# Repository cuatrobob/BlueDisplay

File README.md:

# BlueDisplay
Simple execution for controlling an LED display with Android devices via Bluetooth LE.

The system is controlled by Arduino Uno, the communication is handled by HM-11 Bluetooth 4.0 module, and the display module is DFRobot LCD4884. Since LCD4884 takes up D2 through D7 it will not conflict with the Bluetooth module. In order to monitor serial I/O at the same time, SoftwareSerial was used to redefine the data I/O of BLE communication.

The Android application is capable of running on devices with Android 5.0+ and written with Android Studio 1.2.1.1.

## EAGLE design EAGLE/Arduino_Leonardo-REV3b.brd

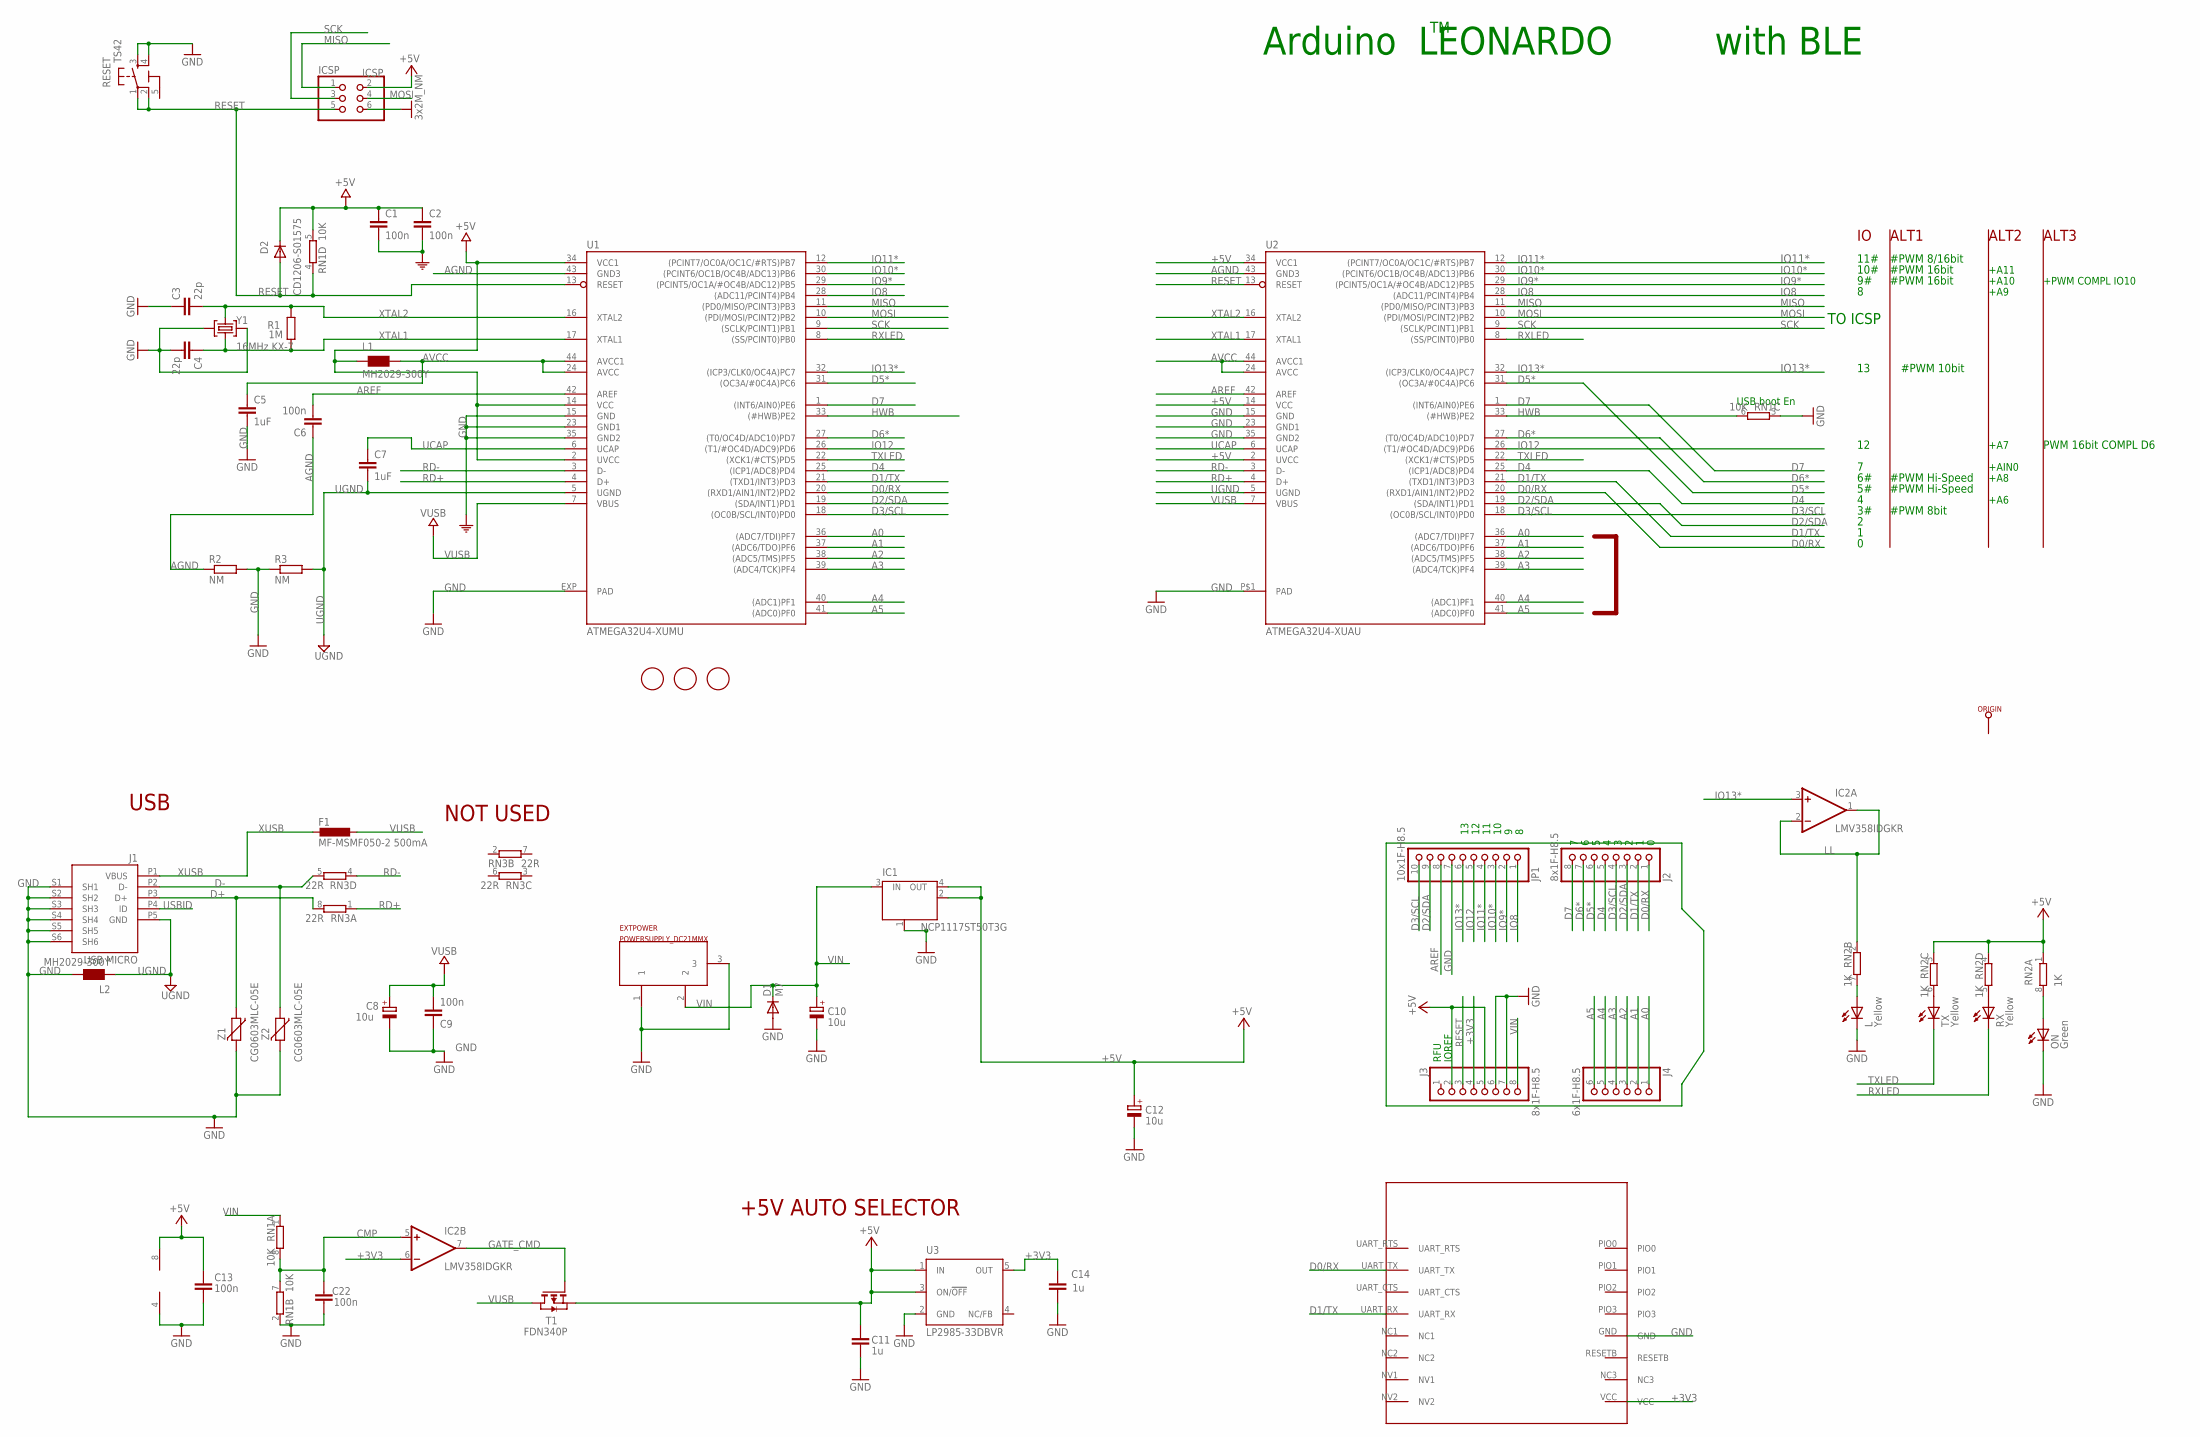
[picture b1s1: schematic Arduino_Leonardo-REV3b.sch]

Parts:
C1, C2, C6, C9, C13, C22: 100n; C0603-ROUND
C3, C4: 22p; C0603-ROUND
C5, C7: 1uF; C0603-ROUND
C8, C10, C12: 10u; SMC_B
C11, C14: 1u; C0603-ROUND
D1: M7; SMB
D2: CD1206-S01575; MINIMELF
EXTPOWER: POWERSUPPLY_DC21MMX; POWERSUPPLY_DC-21MM
F1: MF-MSMF050-2 500mA; L1812
FID1, FID2, FID3: FIDUCIALMOUNT; FIDUCIA-MOUNT
IC1: NCP1117ST50T3G; SOT223
IC2: LMV358IDGKR; MSOP08
ICSP: ICSP; 2X03
J1: USB MICRO; CON2_USB_MICRO_B_AT
J2, J3: 8x1F-H8.5; 1X08
J4: 6x1F-H8.5; 1X06
JP1: 10x1F-H8.5; 1X10
L: Yellow; CHIPLED_0805
L1, L2: MH2029-300Y; 0805
ON: Green; CHIPLED_0805
ORIGIN: TP_SP; TP-SP
R1: 1M; R0603-ROUND
R2, R3: NM; R0402
RESET: TS42
RN1: 10K; CAY16
RN2: 1K; CAY16
RN3: 22R; CAY16
RX: Yellow; CHIPLED_0805
T1: FDN340P; SOT-23
TX: Yellow; CHIPLED_0805
U1: ATMEGA32U4-XUMU; QFN44ML7X7
U2: ATMEGA32U4-XUAU; TQFP44-PAD
U3: LP2985-33DBVR; SOT23-DBV
U$1: HM-11
Y1: 16MHz KX-7; CRYSTAL-3.2-2.5
Z1, Z2: CG0603MLC-05E; CT/CN0603

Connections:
5-GND: RESET.5 (5-GND)
+3V3: C14.2, IC2.6 (-IN), J3.4, U3.5 (OUT)
+5V: C1.1, C2.1, C11.2, C12.+, C13.1, D2.C, IC1.2 (OUT), IC1.4 (OUT), IC2.8 (V+), ICSP.2, J3.2, J3.5, L1.1, RN1.5 (2), RN2.1, RN2.3 (1), RN2.4 (1), T1.2 (S), U1.2 (UVCC), U1.14 (VCC), U1.34 (VCC1), U2.2 (UVCC), U2.14 (VCC), U2.34 (VCC1), U3.1 (IN), U3.3 (ON/!OFF)
A0: J4.1, U1.36 ((ADC7/TDI)PF7), U2.36 ((ADC7/TDI)PF7)
A1: J4.2, U1.37 ((ADC6/TDO)PF6), U2.37 ((ADC6/TDO)PF6)
A2: J4.3, U1.38 ((ADC5/TMS)PF5), U2.38 ((ADC5/TMS)PF5)
A3: J4.4, U1.39 ((ADC4/TCK)PF4), U2.39 ((ADC4/TCK)PF4)
A4: J4.5, U1.40 ((ADC1)PF1), U2.40 ((ADC1)PF1)
A5: J4.6, U1.41 ((ADC0)PF0), U2.41 ((ADC0)PF0)
AGND: C6.1, R2.1, U1.43 (GND3), U2.43 (GND3)
AREF: C6.2, JP1.8, U1.42 (AREF), U2.42 (AREF)
AVCC: C5.1, L1.2, U1.24 (AVCC), U1.44 (AVCC1), U2.24 (AVCC), U2.44 (AVCC1)
CMP: C22.2, IC2.5 (+IN), RN1.7 (2), RN1.8 (2)
D0/RX: J2.1, U1.20 ((RXD1/AIN1/INT2)PD2), U2.20 ((RXD1/AIN1/INT2)PD2), U$1.UART_TX
D1/TX: J2.2, U1.21 ((TXD1/INT3)PD3), U2.21 ((TXD1/INT3)PD3), U$1.UART_RX
D2/SDA: J2.3, JP1.9, U1.19 ((SDA/INT1)PD1), U2.19 ((SDA/INT1)PD1)
D3/SCL: J2.4, JP1.10, U1.18 ((OC0B/SCL/INT0)PD0), U2.18 ((OC0B/SCL/INT0)PD0)
D4: J2.5, U1.25 ((ICP1/ADC8)PD4), U2.25 ((ICP1/ADC8)PD4)
D5*: J2.6, U1.31 ((OC3A/#0C4A)PC6), U2.31 ((OC3A/#0C4A)PC6)
D6*: J2.7, U1.27 ((T0/OC4D/ADC10)PD7), U2.27 ((T0/OC4D/ADC10)PD7)
D7: J2.8, U1.1 ((INT6/AIN0)PE6), U2.1 ((INT6/AIN0)PE6)
D+: J1.P3 (D+), RN3.8 (2), Z1.1
D-: J1.P2 (D-), RN3.5 (2), Z2.1
GATE_CMD: IC2.7 (OUT), T1.3 (G)
GND: C1.2, C2.2, C3.1, C4.2, C5.2, C8.-, C9.1, C10.-, C11.1, C12.-, C13.2, C14.1, C22.1, D1.A, EXTPOWER.1, EXTPOWER.3, IC1.1 (GND/ADJ), IC2.4 (V-), ICSP.6, J1.S1 (SH1), J1.S2 (SH2), J1.S3 (SH3), J1.S4 (SH4), J1.S5 (SH5), J1.S6 (SH6), J3.6, J3.7, JP1.7, L.C, L2.2, ON.C, R2.2, R3.1, RESET.3, RESET.4, RN1.2 (1), RN1.3 (1), U1.15 (GND), U1.23 (GND1), U1.35 (GND2), U1.EXP (PAD), U2.15 (GND), U2.23 (GND1), U2.35 (GND2), U2.P$1 (PAD), U3.2 (GND), Y1.2 (GND), Y1.4 (GND), Z1.2, Z2.2
HWB: RN1.6 (2), U1.33 ((#HWB)PE2), U2.33 ((#HWB)PE2)
IO8: JP1.1, U1.28 ((ADC11/PCINT4)PB4), U2.28 ((ADC11/PCINT4)PB4)
IO9*: JP1.2, U1.29 ((PCINT5/OC1A/#OC4B/ADC12)PB5), U2.29 ((PCINT5/OC1A/#OC4B/ADC12)PB5)
IO10*: JP1.3, U1.30 ((PCINT6/OC1B/OC4B/ADC13)PB6), U2.30 ((PCINT6/OC1B/OC4B/ADC13)PB6)
IO11*: JP1.4, U1.12 ((PCINT7/OC0A/OC1C/#RTS)PB7), U2.12 ((PCINT7/OC0A/OC1C/#RTS)PB7)
IO12: JP1.5, U1.26 ((T1/#OC4D/ADC9)PD6), U2.26 ((T1/#OC4D/ADC9)PD6)
IO13*: IC2.3 (+IN), JP1.6, U1.32 ((ICP3/CLK0/OC4A)PC7), U2.32 ((ICP3/CLK0/OC4A)PC7)
LL: IC2.1 (OUT), IC2.2 (-IN), RN2.2 (1)
MISO: ICSP.1, U1.11 ((PD0/MISO/PCINT3)PB3), U2.11 ((PD0/MISO/PCINT3)PB3)
MOSI: ICSP.4, U1.10 ((PDI/MOSI/PCINT2)PB2), U2.10 ((PDI/MOSI/PCINT2)PB2)
unnamed: L.A, RN2.7 (2)
unnamed: ON.A, RN2.8 (2)
unnamed: RN2.6 (2), TX.A
unnamed: RN2.5 (2), RX.A
RD+: RN3.1, U1.4 (D+), U2.4 (D+)
RD-: RN3.4 (1), U1.3 (D-), U2.3 (D-)
RESET: D2.A, ICSP.5, J3.3, RESET.1, RESET.2, RN1.4 (1), U1.13 (RESET), U2.13 (RESET)
RXLED: RX.C, U1.8 ((SS/PCINT0)PB0), U2.8 ((SS/PCINT0)PB0)
SCK: ICSP.3, U1.9 ((SCLK/PCINT1)PB1), U2.9 ((SCLK/PCINT1)PB1)
TXLED: TX.C, U1.22 ((XCK1/#CTS)PD5), U2.22 ((XCK1/#CTS)PD5)
UCAP: C7.1, U1.6 (UCAP), U2.6 (UCAP)
UGND: C7.2, J1.P5 (GND), L2.1, R3.2, U1.5 (UGND), U2.5 (UGND)
USBID: J1.P4 (ID)
VIN: C10.+, D1.C, EXTPOWER.2, IC1.3 (IN), J3.8, RN1.1
VUSB: C8.+, C9.2, F1.1, T1.1 (D), U1.7 (VBUS), U2.7 (VBUS)
XTAL1: C4.1, R1.1, U1.17 (XTAL1), U2.17 (XTAL1), Y1.1 (C1)
XTAL2: C3.2, R1.2, U1.16 (XTAL2), U2.16 (XTAL2), Y1.3 (C2)
XUSB: F1.2, J1.P1 (VBUS)

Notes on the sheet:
Arduino LEONARDO
USB boot En
USB
+5V AUTO SELECTOR
NOT USED
TO ICSP
10#
11#
#PWM 8bit
#PWM Hi-Speed
#PWM 8/16bit
#PWM 16bit
PWM 16bit COMPL D6
#PWM 10bit
+A6
+A7
IOREF
RFU
+A11
+A10
+A8
+A9
+PWM COMPL IO10
+AIN0
ALT1
ALT2
ALT3
with BLE

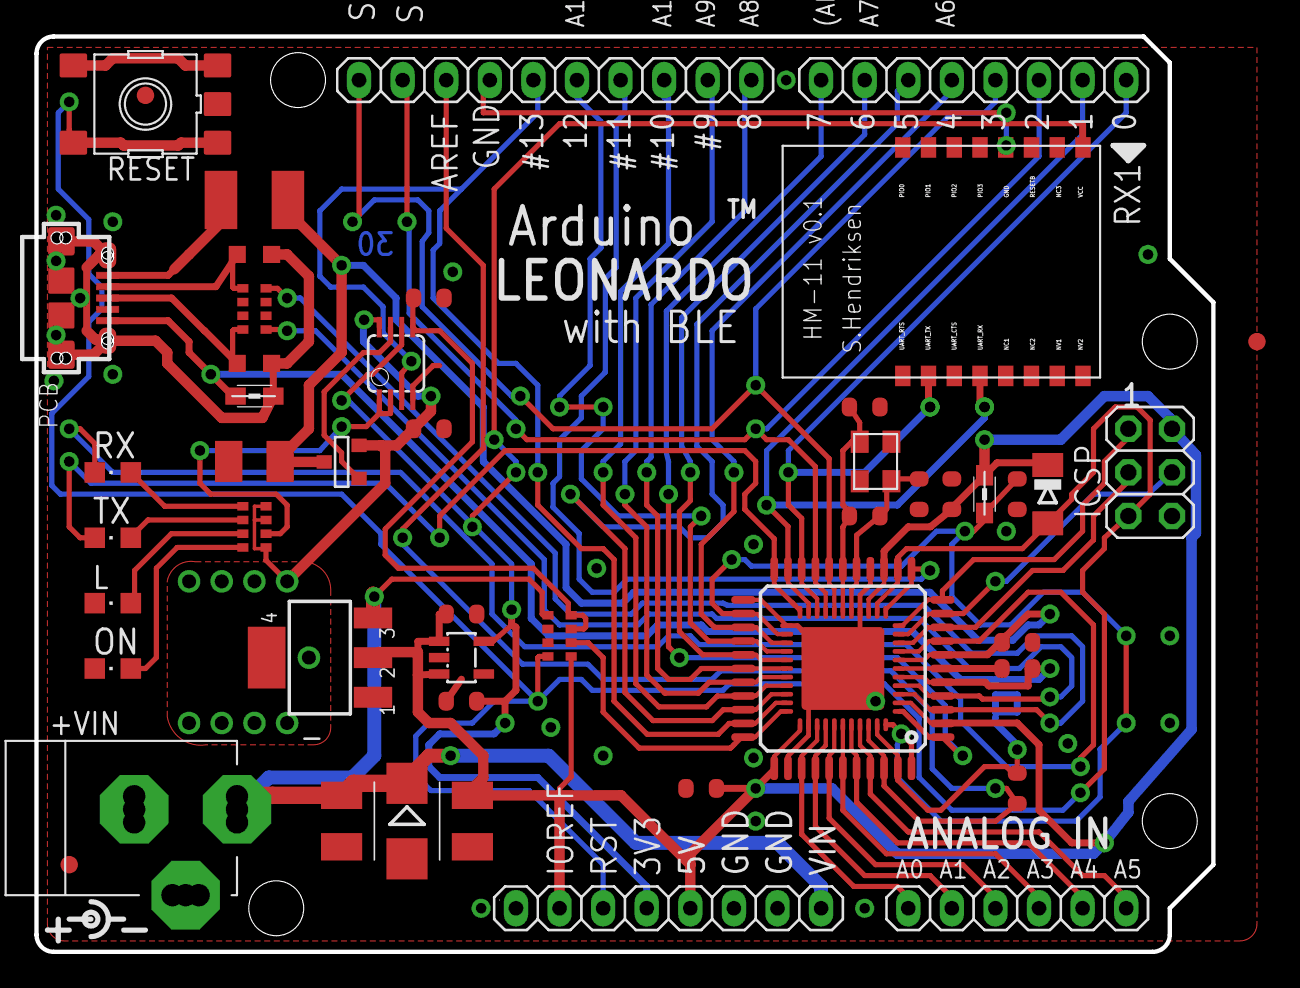
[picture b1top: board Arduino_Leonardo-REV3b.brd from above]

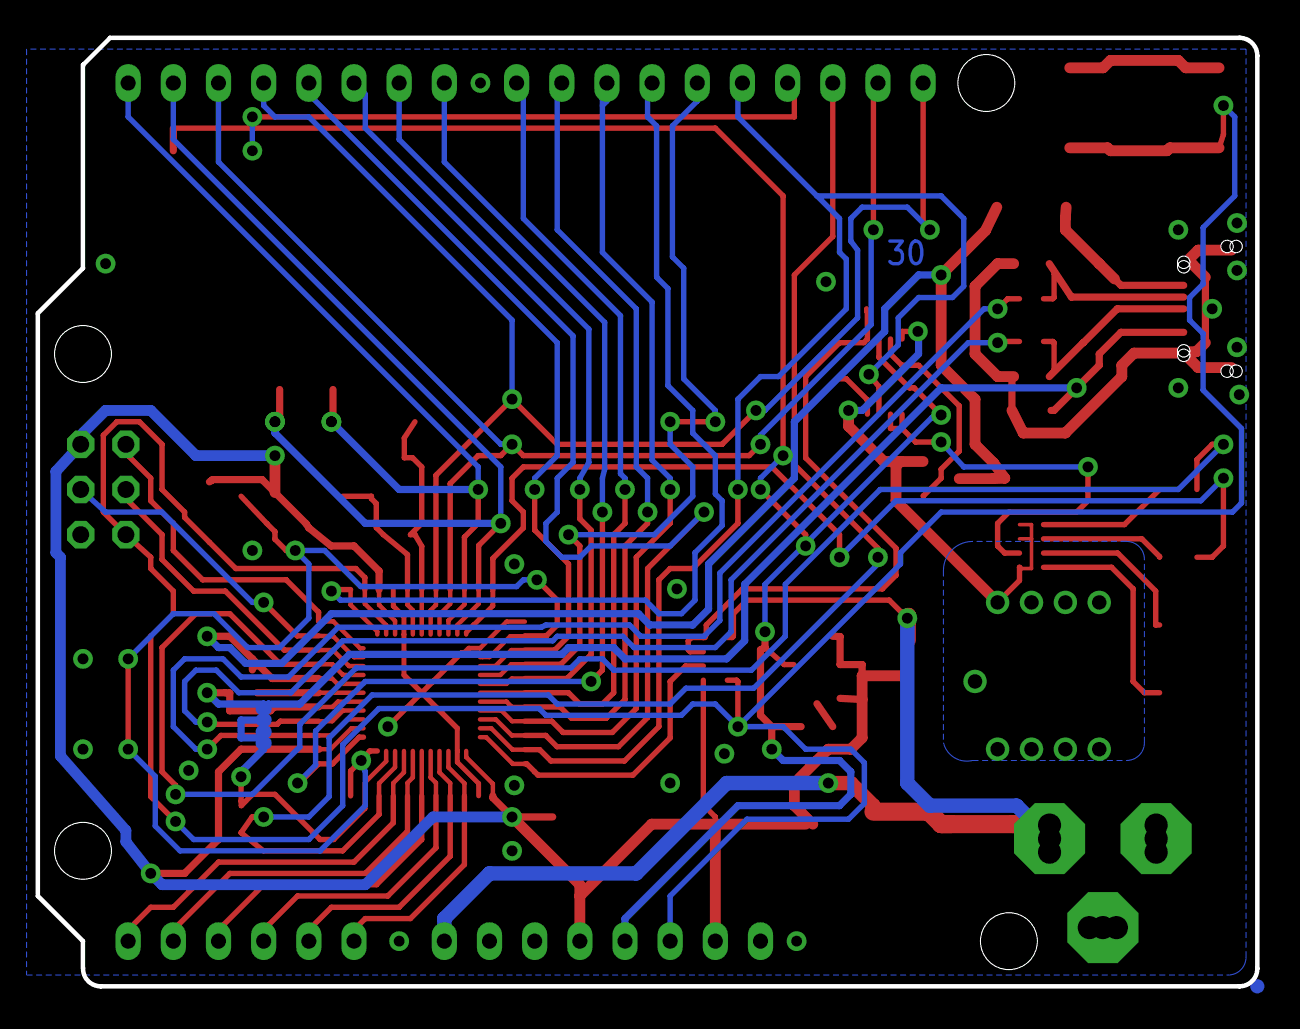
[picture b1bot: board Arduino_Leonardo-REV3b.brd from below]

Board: 2 copper layers, 68.6 x 53.3 mm, 52 parts (2 on the bottom side), 51 nets.

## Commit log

2015-06-08 Initial commit.
2015-06-08 Removed the board files.
2015-06-08 Add license.
2015-06-13 Renamed Arduino application.
2015-06-13 Uploaded signed APK.
